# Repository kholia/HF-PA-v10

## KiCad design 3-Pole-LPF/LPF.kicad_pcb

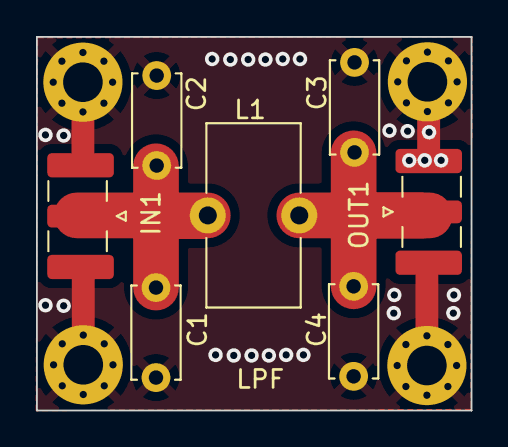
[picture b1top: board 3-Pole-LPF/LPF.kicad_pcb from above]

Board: 2 copper layers, 24.1 x 20.8 mm, 11 parts (0 on the bottom side), 3 nets.

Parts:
C1, C2, C3, C4: 100n; C_Disc_D5.0mm_W2.5mm_P5.00mm
H1, H2, H3, H4: MountingHole_Pad; MountingHole_2.2mm_M2_Pad_Via
IN1: SMA; SMA_Samtec_SMA-J-P-H-ST-EM1_EdgeMount
L1: L_Small; L_Toroid_Vertical_L10.0mm_W5.0mm_P5.08mm
OUT1: SMA; SMA_Samtec_SMA-J-P-H-ST-EM1_EdgeMount

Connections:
GND: C1.2, C2.2, C3.2, C4.2, H1.1, H2.1, H3.1, H4.1, IN1.2 (Ext), OUT1.2 (Ext)
unnamed: C1.1, C2.1, IN1.1 (In), L1.1
unnamed: C3.1, C4.1, L1.2, OUT1.1 (In)

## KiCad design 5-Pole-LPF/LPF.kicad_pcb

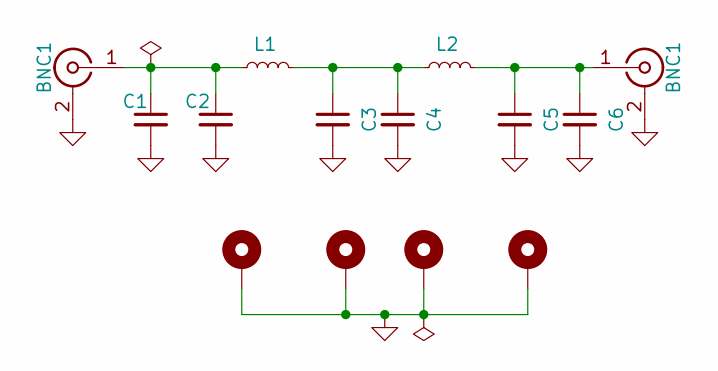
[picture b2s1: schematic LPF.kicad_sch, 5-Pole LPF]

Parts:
BNC1: SMA; SMA_Samtec_SMA-J-P-H-ST-EM1_EdgeMount
C1, C2, C3, C4, C5, C6: 100n; C_Disc_D5.0mm_W2.5mm_P5.00mm
H1, H2, H3, H4: MountingHole_Pad; MountingHole_2.2mm_M2_Pad_Via
L1, L2: L_Small; L_Toroid_Vertical_L10.0mm_W5.0mm_P5.08mm

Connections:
GND: C1.2, C2.2, C3.2, C4.2, C5.2, C6.2, H1.1, H2.1, H3.1, H4.1; also elsewhere on the board
unnamed: C3.1, C4.1, L1.2, L2.1
unnamed 2: C1.1, C2.1, L1.1; also elsewhere on the board
unnamed 3: C5.1, C6.1, L2.2; also elsewhere on the board

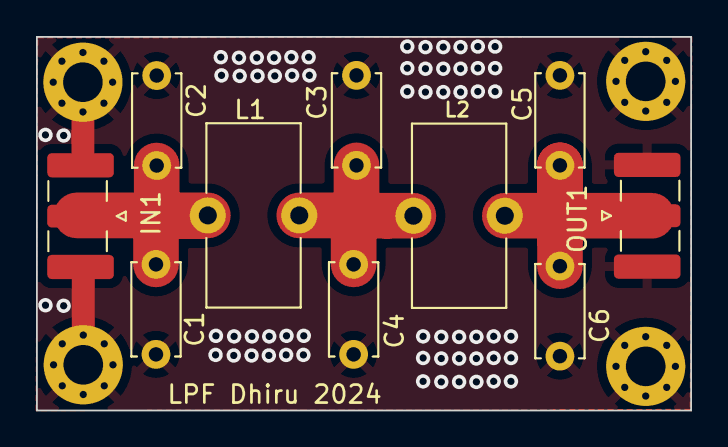
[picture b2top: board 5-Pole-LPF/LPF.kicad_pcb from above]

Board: 2 copper layers, 36.3 x 20.8 mm, 14 parts (0 on the bottom side), 4 nets.

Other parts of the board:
IN1: SMA; SMA_Samtec_SMA-J-P-H-ST-EM1_EdgeMount
OUT1: SMA; SMA_Samtec_SMA-J-P-H-ST-EM1_EdgeMount

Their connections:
GND: IN1.2 (Ext), OUT1.2 (Ext); also elsewhere on the board
unnamed 2: IN1.1 (In); also elsewhere on the board
unnamed 3: OUT1.1 (In); also elsewhere on the board

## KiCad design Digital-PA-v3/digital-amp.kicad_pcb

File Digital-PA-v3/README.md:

# Digital-PA
A digital mode power amplifier for 160-10m.
Created using Kicad 7.0.6.

Licensed under Attribution-NonCommercial 4.0 (CC BY-NC 4.0).

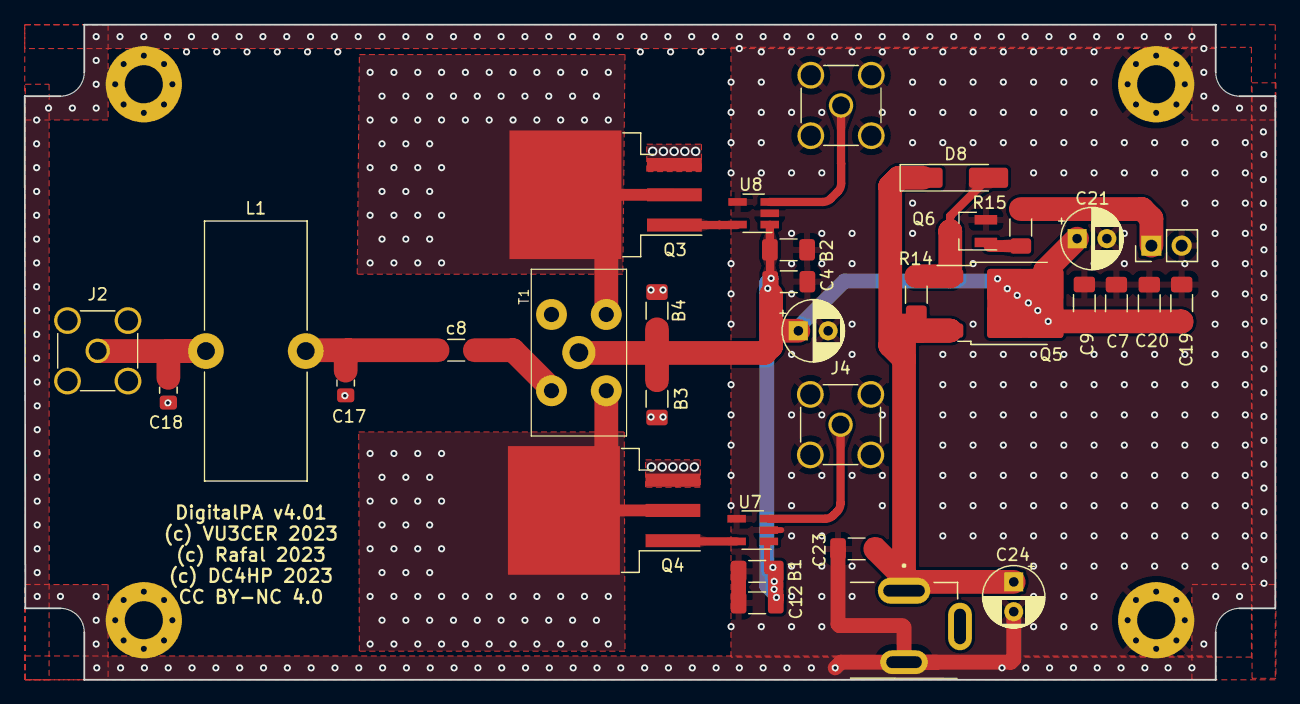
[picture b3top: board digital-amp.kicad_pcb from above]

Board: 2 copper layers, 105.0 x 55.0 mm, 37 parts (0 on the bottom side), 15 nets.

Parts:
B1, B2, B3, B4: 0.1uF; C_1206_3216Metric_Pad1.33x1.80mm_HandSolder
C4, C7, C12, C19: 1n; C_1206_3216Metric_Pad1.33x1.80mm_HandSolder
C9, C20, C23: 100n; C_1206_3216Metric_Pad1.33x1.80mm_HandSolder
C10, C21, C24: 100u; CP_Radial_D5.0mm_P2.50mm
C17, C18: 100p; C_0805_2012Metric_Pad1.18x1.45mm_HandSolder
D8: 5.1V; D_MiniMELF_Handsoldering
H1, H2, H3, H4: MountingHole_Pad; MountingHole_3.2mm_M3_Pad_Via
J1, J2, J4: Conn_Coaxial; SMA_Amphenol_901-144_Vertical
J3: Conn_01x02_Male; PinHeader_1x02_P2.54mm_Vertical
L1: 318.5nH; L_Toroid_Vertical_L21.6mm_W8.4mm_P8.38mm_Pulse_G
Power1: DC-005 (Barrel Jack); XKB_DC-005-5A-2.0_Modded
Q3, Q4: IRF510; TO-263-3_TabPin2
Q5: AOD407; TO-252-2
Q6: 2N3904; SOT-23_Handsoldering
R14: 100k; R_1206_3216Metric_Pad1.30x1.75mm_HandSolder
R15: 4.7k; R_1206_3216Metric_Pad1.30x1.75mm_HandSolder
T1: BN-61-202, 2+2T:6T; BN202V
U7, U8: UCC27517DBVR; SOT-23-5_HandSoldering
c8: 0.1uF; C_1206_3216Metric_Pad1.33x1.80mm_HandSolder

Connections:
GND: B1.1, B2.1, B3.1, B4.1, C4.2, C7.2, C9.2, C10.2, C12.2, C17.2, C18.2, C19.2, C20.2, C21.2, C23.2, C24.2, H1.1, H2.1, H3.1, H4.1, J1.2 (Ext), J2.2 (Ext), J3.2, J4.2 (Ext), Power1.2, Q3.3 (S), Q4.3 (S), Q6.2 (E), T1.5, U7.2 (GND), U7.4 (IN-), U8.2 (GND), U8.4 (IN-)
unnamed: C17.1, L1.1, c8.1
unnamed: D8.2 (A), Q5.1 (G), Q6.3 (C), R14.2
unnamed: J1.1 (In), U8.3 (IN+)
unnamed: C18.1, J2.1 (In), L1.2
unnamed: J4.1 (In), U7.3 (IN+)
unnamed: Q3.2 (D), T1.1
unnamed: Q3.1 (G), U8.5 (OUT)
unnamed: Q4.2 (D), T1.3
unnamed: Q4.1 (G), U7.5 (OUT)
unnamed: Q6.1 (B), R15.1
unnamed: T1.4, c8.2
PTT: J3.1, R15.2
VDC: B1.2, B2.2, B3.2, B4.2, C4.1, C7.1, C9.1, C10.1, C12.1, C19.1, C20.1, C21.1, Q5.2 (D), T1.2, U7.1 (VDD), U8.1 (VDD)
VIN: C23.1, C24.1, D8.1 (K), Power1.1, Q5.3 (S), R14.1

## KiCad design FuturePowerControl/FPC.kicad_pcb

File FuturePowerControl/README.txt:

https://electronics.stackexchange.com/questions/630076/buck-converter-adjustable-output-voltage-using-digital-potentiometer

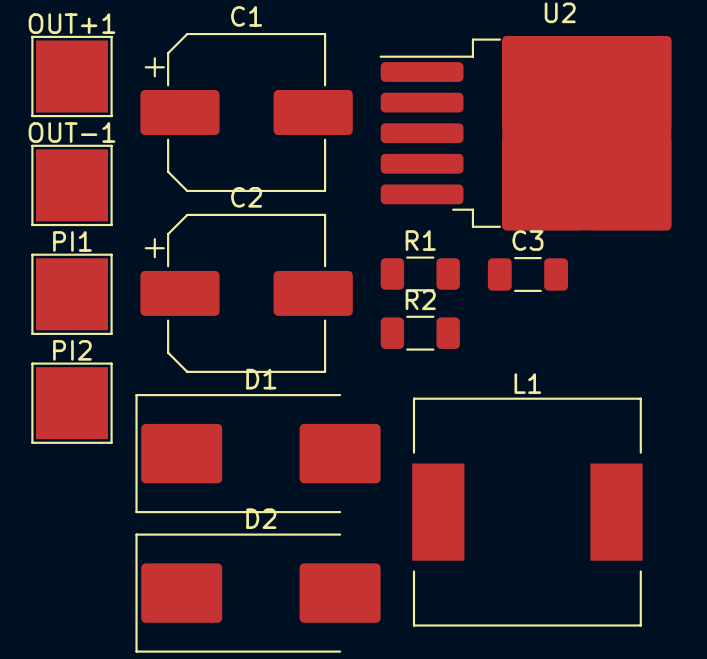
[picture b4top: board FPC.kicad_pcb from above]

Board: 2 copper layers, 13 parts (0 on the bottom side), 6 nets, no tracks yet.

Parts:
C1: 220u; CP_Elec_8x10.5
C2: 470uF; CP_Elec_8x10.5
C3: 100n; C_1206_3216Metric_Pad1.33x1.80mm_HandSolder
D1, D2: SS54; D_SMC_Handsoldering
L1: 68uH; L_12x12mm_H6mm
OUT+1: OVDC; TestPoint_Pad_4.0x4.0mm
OUT-1: GND; TestPoint_Pad_4.0x4.0mm
PI1: VDC; TestPoint_Pad_4.0x4.0mm
PI2: GND; TestPoint_Pad_4.0x4.0mm
R1: 270; R_1206_3216Metric_Pad1.30x1.75mm_HandSolder
R2: 5k; R_1206_3216Metric_Pad1.30x1.75mm_HandSolder
U2: LM2596S-ADJ; TO-263-5_TabPin3

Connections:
+VDC: D2.2 (A), PI1.1
GND: C1.2, C2.2, C3.2, D1.2 (A), OUT-1.1, PI2.1, R1.2, U2.3 (GND), U2.5 (~ON/OFF)
unnamed: D1.1 (K), L1.1, U2.2 (OUT)
unnamed: C2.1, D2.1 (K), U2.1 (VIN)
unnamed: C1.1, C3.1, L1.2, OUT+1.1, R2.1
unnamed: R2.2, U2.4 (FB)

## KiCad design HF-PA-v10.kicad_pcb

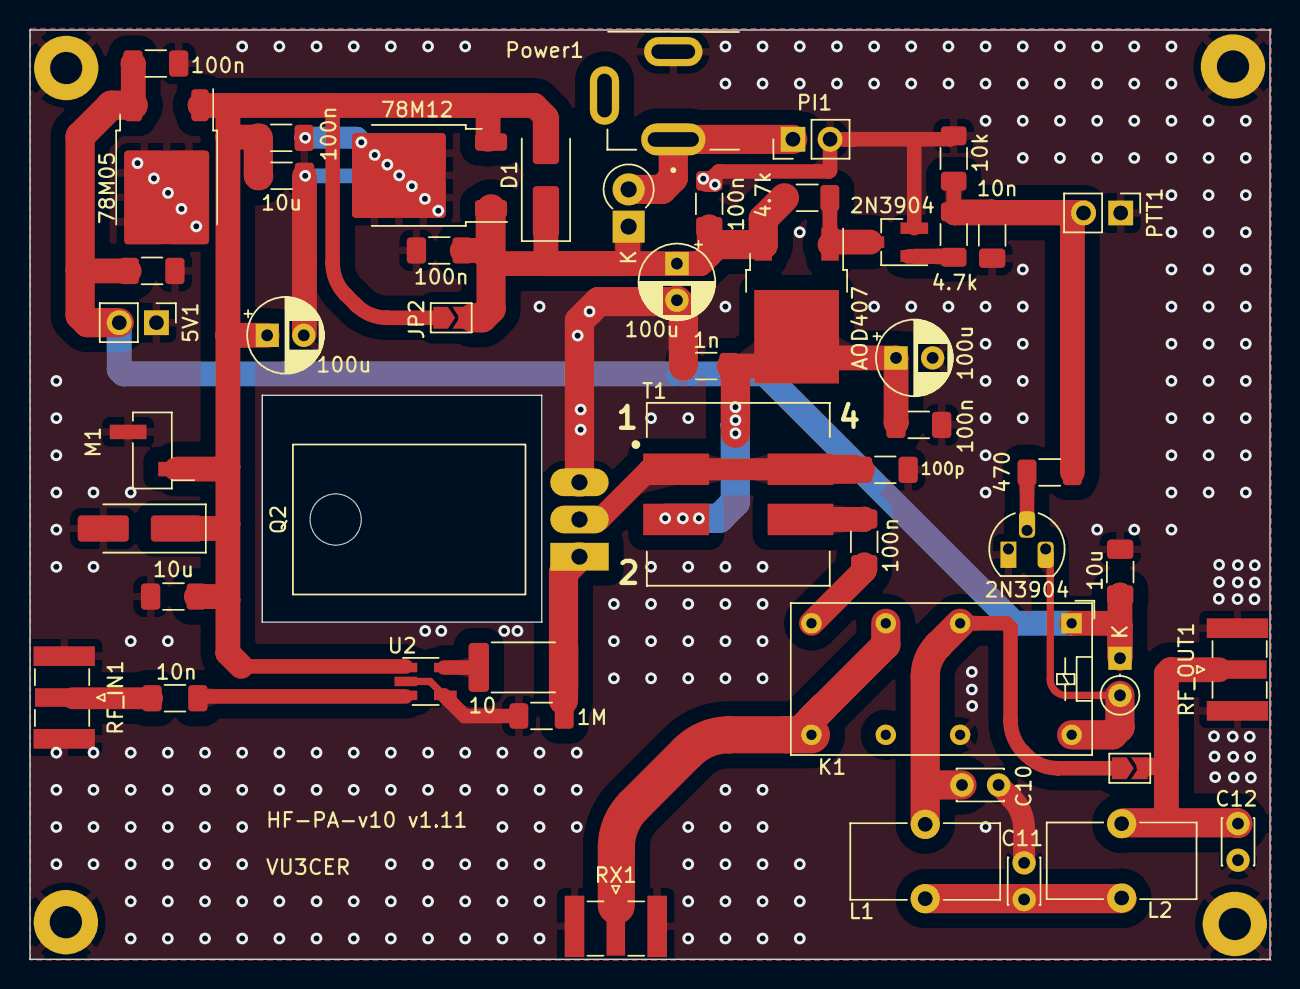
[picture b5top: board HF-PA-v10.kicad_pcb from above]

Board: 2 copper layers, 84.7 x 63.5 mm, 55 parts (0 on the bottom side), 22 nets.

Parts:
5V1: 5V; PinHeader_1x02_P2.54mm_Vertical
C1, C6, C7, C9, C14, C18: 100n; C_1206_3216Metric_Pad1.33x1.80mm_HandSolder
C2, C8, C13, C16: 10u; C_1206_3216Metric_Pad1.33x1.80mm_HandSolder
C3: 100p; C_1206_3216Metric_Pad1.33x1.80mm_HandSolder
C4, C19: 10n; C_1206_3216Metric_Pad1.33x1.80mm_HandSolder
C5, C15, C20: 100u; CP_Radial_D5.0mm_P2.50mm
C10, C12: 120p; C_Disc_D3.0mm_W2.0mm_P2.50mm
C11: 200p; C_Disc_D3.0mm_W2.0mm_P2.50mm
C17: 1n; C_1206_3216Metric_Pad1.33x1.80mm_HandSolder
D1: 1N4007; D_SMA_Handsoldering
D2: M7 (1N4007); D_SMA_Handsoldering
D3: 1N4148; D_DO-35_SOD27_P2.54mm_Vertical_KathodeUp
D4: 2A+ Schottky (1N5822 / SR2100); D_DO-41_SOD81_P2.54mm_Vertical_KathodeUp
H1, H2, H3, H4: MountingHole_Pad; MountingHole_2.2mm_M2_Pad
JP1, JP2: Jumper_2_Open; SolderJumper-2_P1.3mm_Open_TrianglePad1.0x1.5mm
K1: Omron G5V-2 / OEN 46-05-2C; Relay_DPDT_Omron_G5V-2
L1, L2: 360n; L_Toroid_Vertical_L10.0mm_W5.0mm_P5.08mm
M1: Fan; PinHeader_1x02_P2.54mm_Vertical_SMD_Pin1Left
PI1: VDC; PinHeader_1x02_P2.54mm_Vertical
PTT1: PTT; PinHeader_1x02_P2.54mm_Vertical
Power1: DC-005 (Barrel Jack); XKB_DC-005-5A-2.0_Modded
Q1: 2N3904; TO-92_HandSolder
Q2: IRF510; TO-220-3_Horizontal_TabDown
Q3: AOD407; TO-252-2
Q4: 2N3904; SOT-23_Handsoldering
R1: 1M; R_1206_3216Metric_Pad1.30x1.75mm_HandSolder
R2: 10k; R_1206_3216Metric_Pad1.30x1.75mm_HandSolder
R3: 10; R_2512_6332Metric_Pad1.40x3.35mm_HandSolder
R4: 470; R_1206_3216Metric_Pad1.30x1.75mm_HandSolder
R8, R9: 4.7k; R_1206_3216Metric_Pad1.30x1.75mm_HandSolder
RF_IN1: SMA; SMA_Samtec_SMA-J-P-X-ST-EM1_EdgeMount
RF_OUT1: SMA; SMA_Samtec_SMA-J-P-X-ST-EM1_EdgeMount
RX1: SMA; SMA_Samtec_SMA-J-P-X-ST-EM1_EdgeMount
T1: Bifilar XFMR; IND_SRF1260A-4R7Y
U1: 78M05; TO-252-2
U2: UCC27517DBVR; SOT-23-5_HandSoldering
U3: 78M12; TO-252-2

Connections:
12V: C1.1, C2.1, C16.1, C20.1, D1.2 (A), D2.1 (K), JP2.1 (A), M1.1 (+), U1.1 (VI), U2.1 (VDD), U3.3 (OUT)
+5V: 5V1.2, C8.1, C9.1, C13.1, D3.1 (K), K1.1, U1.3 (VO)
+VDC: D4.2 (A), PI1.1, Power1.1
/DRAIN: C3.1, Q2.2 (D), T1.1, T1.4
GND: 5V1.1, C1.2, C2.2, C3.2, C4.2, C5.2, C6.2, C8.2, C9.2, C10.2, C11.2, C12.2, C13.2, C14.2, C15.2, C16.2, C17.2, C18.2, C20.2, D2.2 (A), H1.1, H2.1, H3.1, H4.1, K1.13, M1.2 (-), PI1.2, PTT1.1, Power1.2, Q1.1 (E), Q2.3 (S), Q4.2 (E), R1.2, R2.2, RF_IN1.2 (Ext), RF_OUT1.2 (Ext), RX1.2 (Ext), U1.2 (GND), U2.2 (GND), U2.4 (IN-), U3.2 (GND)
LPF: C10.1, JP1.1 (A), K1.4, L1.1
unnamed: C7.2, T1.3
unnamed: C11.1, L1.2, L2.1
unnamed: C14.1, C15.1, C18.1, D1.1 (K), D4.1 (K), JP2.2 (B), Q3.3 (S), R8.2, U3.1 (IN)
unnamed: D3.2 (A), K1.16, Q1.3 (C)
unnamed: C12.1, JP1.2 (B), L2.2, RF_OUT1.1 (In)
unnamed: Q1.2 (B), R4.2
unnamed: Q2.1 (G), R1.1, R3.1
unnamed: C5.1, C6.1, C17.1, Q3.2 (D), T1.2
unnamed: Q3.1 (G), Q4.3 (C), R8.1
unnamed: Q4.1 (B), R9.1
unnamed: C19.1, RF_IN1.1 (In)
unnamed: C19.2, U2.3 (IN+)
unnamed: R3.2, U2.5 (OUT)
PTT: C4.1, PTT1.2, R2.1, R4.1, R9.2
RF_OUT: C7.1, K1.8
RX: K1.6, K1.9, RX1.1 (In)

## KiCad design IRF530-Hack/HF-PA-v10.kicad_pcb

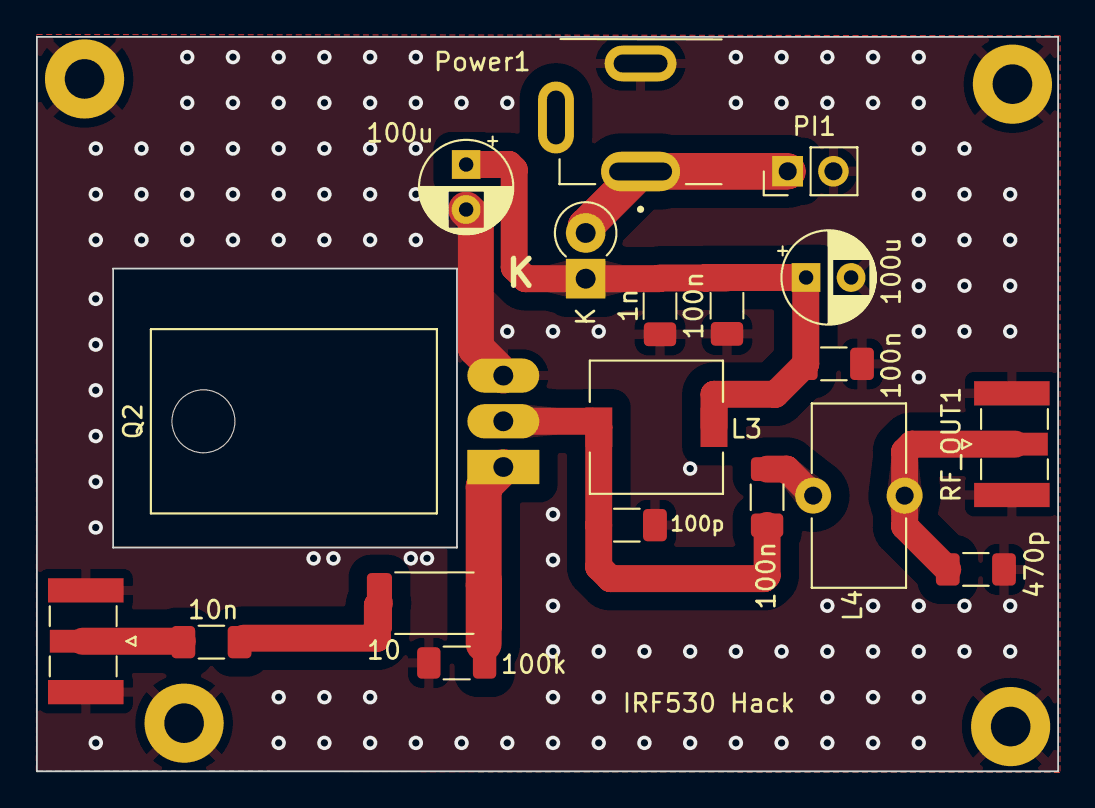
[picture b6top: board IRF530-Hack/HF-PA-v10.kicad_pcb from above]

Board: 2 copper layers, 56.7 x 40.8 mm, 23 parts (0 on the bottom side), 9 nets.

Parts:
C1: 470p; C_1206_3216Metric_Pad1.33x1.80mm_HandSolder
C3: 100p; C_1206_3216Metric_Pad1.33x1.80mm_HandSolder
C5, C15: 100u; CP_Radial_D5.0mm_P2.50mm
C6, C7, C14: 100n; C_1206_3216Metric_Pad1.33x1.80mm_HandSolder
C17: 1n; C_1206_3216Metric_Pad1.33x1.80mm_HandSolder
C19: 10n; C_1206_3216Metric_Pad1.33x1.80mm_HandSolder
D4: 2A+ Schottky (1N5822 / SR2100); D_DO-41_SOD81_P2.54mm_Vertical_KathodeUp
H1, H2, H3, H4: MountingHole_Pad; MountingHole_2.2mm_M2_Pad
L3: 3.3uH / 4.7uH; L_7.3x7.3_H3.5
L4: 240n; L_Toroid_Vertical_L10.0mm_W5.0mm_P5.08mm
PI1: VDC; PinHeader_1x02_P2.54mm_Vertical
Power1: DC-005 (Barrel Jack); XKB_DC-005-5A-2.0_Modded
Q2: IRF530; TO-220-3_Horizontal_TabDown
R1: 100k; R_1206_3216Metric_Pad1.30x1.75mm_HandSolder
R3: 10; R_2512_6332Metric_Pad1.40x3.35mm_HandSolder
RF_IN1: SMA; SMA_Samtec_SMA-J-P-X-ST-EM1_EdgeMount
RF_OUT1: SMA; SMA_Samtec_SMA-J-P-X-ST-EM1_EdgeMount

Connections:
+VDC: D4.2 (A), PI1.1, Power1.1
/DRAIN: C3.1, C7.2, L3.2, Q2.2 (D)
GND: C1.2, C3.2, C5.2, C6.2, C14.2, C15.2, C17.2, H1.1, H2.1, H3.1, H4.1, PI1.2, Power1.2, Q2.3 (S), R1.2, RF_IN1.2 (Ext), RF_OUT1.2 (Ext)
unnamed: C7.1, L4.1
unnamed: C19.2, R3.2
unnamed: C5.1, C6.1, C14.1, C15.1, C17.1, D4.1 (K), L3.1
unnamed: Q2.1 (G), R1.1, R3.1
unnamed: C19.1, RF_IN1.1 (In)
unnamed: C1.1, L4.2, RF_OUT1.1 (In)

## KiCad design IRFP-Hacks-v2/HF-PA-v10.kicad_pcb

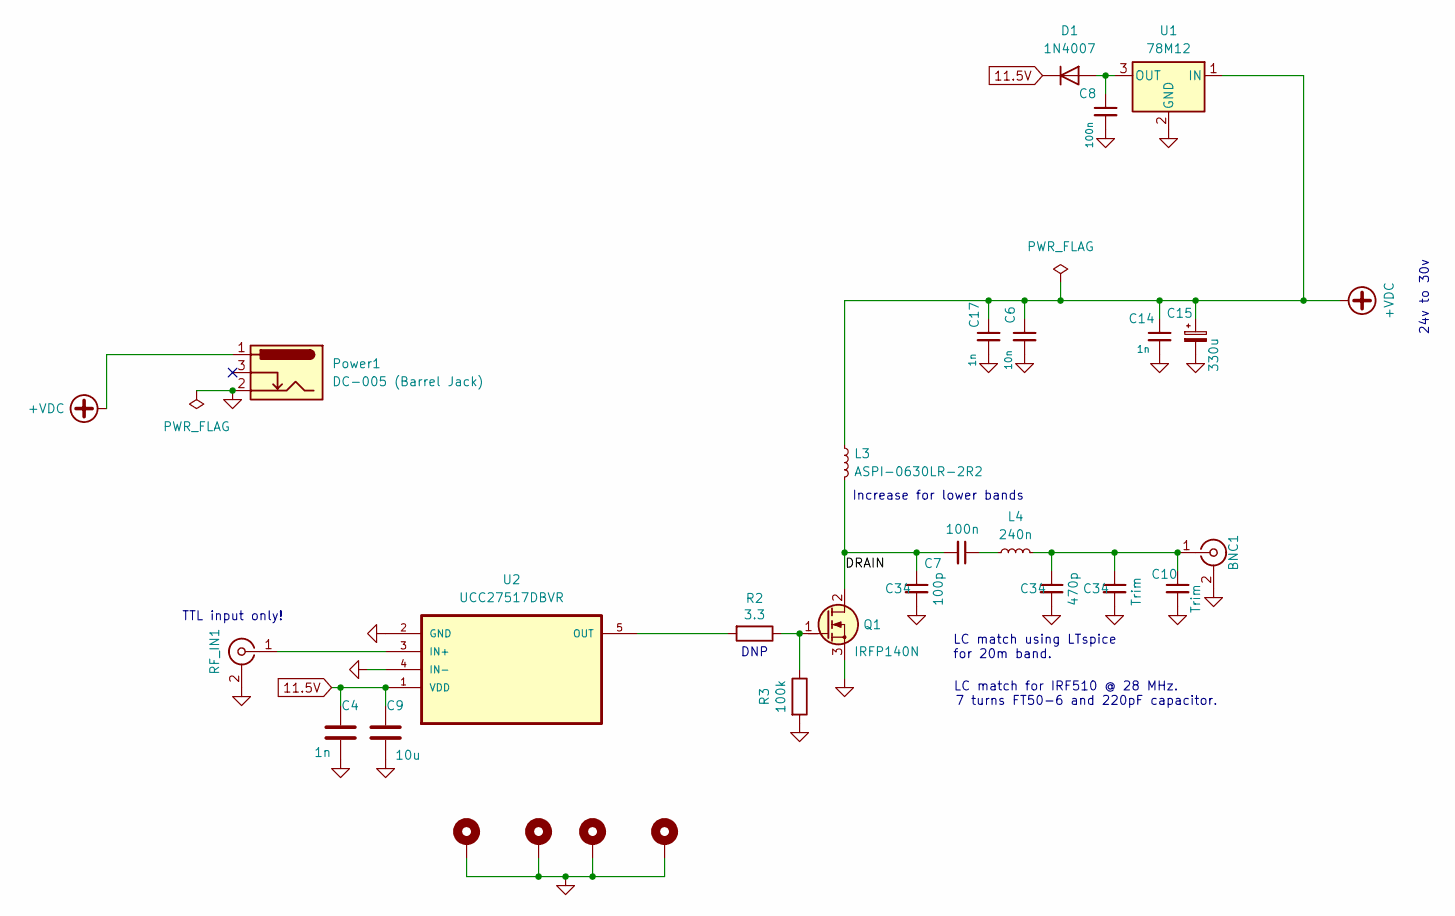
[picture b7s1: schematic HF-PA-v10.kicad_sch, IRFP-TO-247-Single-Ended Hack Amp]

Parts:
BNC1: SMA; SMA_Samtec_SMA-J-P-X-ST-EM1_EdgeMount
C4, C14, C17: 1n; C_1206_3216Metric_Pad1.33x1.80mm_HandSolder
C6: 10n; C_1206_3216Metric_Pad1.33x1.80mm_HandSolder
C7, C8: 100n; C_1206_3216Metric_Pad1.33x1.80mm_HandSolder
C9: 10u; C_1206_3216Metric_Pad1.33x1.80mm_HandSolder
C10: Trim; C_1206_3216Metric_Pad1.33x1.80mm_HandSolder
C15: 330u; CP_Radial_D8.0mm_P5.00mm
C34: 100p; C_1206_3216Metric_Pad1.33x1.80mm_HandSolder
D1: 1N4007; D_DO-41_SOD81_P2.54mm_Vertical_KathodeUp
H1, H2, H3, H4: MountingHole_Pad; MountingHole_3.2mm_M3_Pad_Via
L3: ASPI-0630LR-2R2; L_7.3x7.3_H3.5
L4: 240n; L_Toroid_Vertical_L10.0mm_W5.0mm_P5.08mm
Power1: DC-005 (Barrel Jack); XKB_DC-005-5A-2.0_Modded
Q1: IRFP140N; TO-247-3_Horizontal_TabDown_Modded
R2: 3.3; R_1206_3216Metric_Pad1.30x1.75mm_HandSolder
R3: 100k; R_1206_3216Metric_Pad1.30x1.75mm_HandSolder
RF_IN1: SMA; SMA_Samtec_SMA-J-P-X-ST-EM1_EdgeMount
U1: 78M12; TO-252-2-Longer
U2: UCC27517DBVR; SOT-23-5_HandSoldering

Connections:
11.5V: C4.1, C9.1, D1.1 (K), U2.1 (VDD)
+VDC: C6.1, C14.1, C15.1, C17.1, L3.1, Power1.1, U1.1 (IN)
/DRAIN: C7.2, L3.2, Q1.2 (D); also elsewhere on the board
GND: C4.2, C6.2, C8.2, C9.2, C10.2, C14.2, C15.2, C17.2, H1.1, H2.1, H3.1, H4.1, Power1.2, Q1.3 (S), R3.2, RF_IN1.2 (Ext), U1.2 (GND), U2.2 (GND), U2.4 (IN-); also elsewhere on the board
unnamed: C7.1, L4.1
unnamed: C8.1, D1.2 (A), U1.3 (OUT)
unnamed: Q1.1 (G), R2.1, R3.1
unnamed: RF_IN1.1 (In), U2.3 (IN+)
unnamed 8: C10.1, L4.2; also elsewhere on the board
unnamed: R2.2, U2.5 (OUT)

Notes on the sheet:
DNP
TTL input only!
LC match for IRF510 @ 28 MHz. 7 turns FT50-6 and 220pF capacitor.
LC match using LTspice for 20m band.
24v to 30v
Increase for lower bands

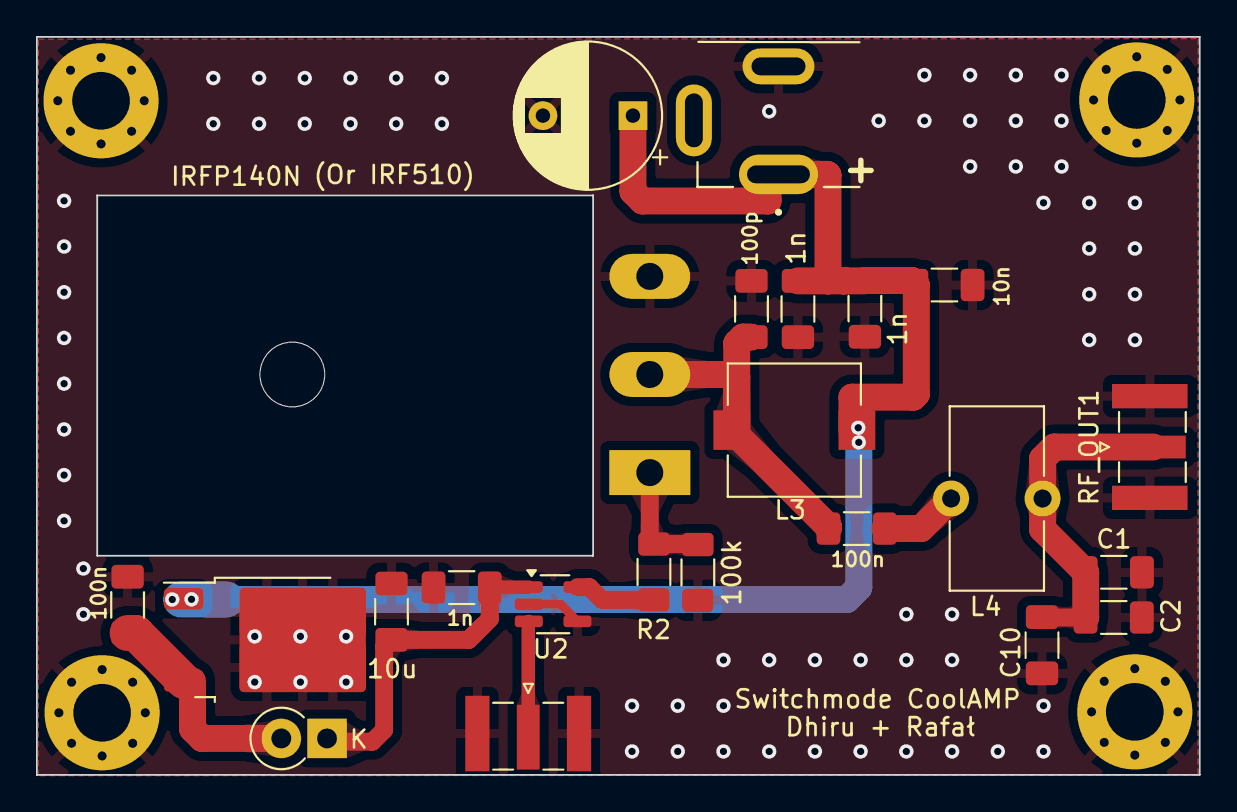
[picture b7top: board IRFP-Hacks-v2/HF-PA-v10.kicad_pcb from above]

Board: 2 copper layers, 64.6 x 41.0 mm, 27 parts (0 on the bottom side), 10 nets.

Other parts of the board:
C1: 470p; C_1206_3216Metric_Pad1.33x1.80mm_HandSolder
C2: Trim; C_1206_3216Metric_Pad1.33x1.80mm_HandSolder
C3: 100p; C_1206_3216Metric_Pad1.33x1.80mm_HandSolder
RF_OUT1: SMA; SMA_Samtec_SMA-J-P-X-ST-EM1_EdgeMount

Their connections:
/DRAIN: C3.1; also elsewhere on the board
GND: C1.2, C2.2, C3.2, RF_OUT1.2 (Ext); also elsewhere on the board
unnamed 8: C1.1, C2.1, RF_OUT1.1 (In); also elsewhere on the board
